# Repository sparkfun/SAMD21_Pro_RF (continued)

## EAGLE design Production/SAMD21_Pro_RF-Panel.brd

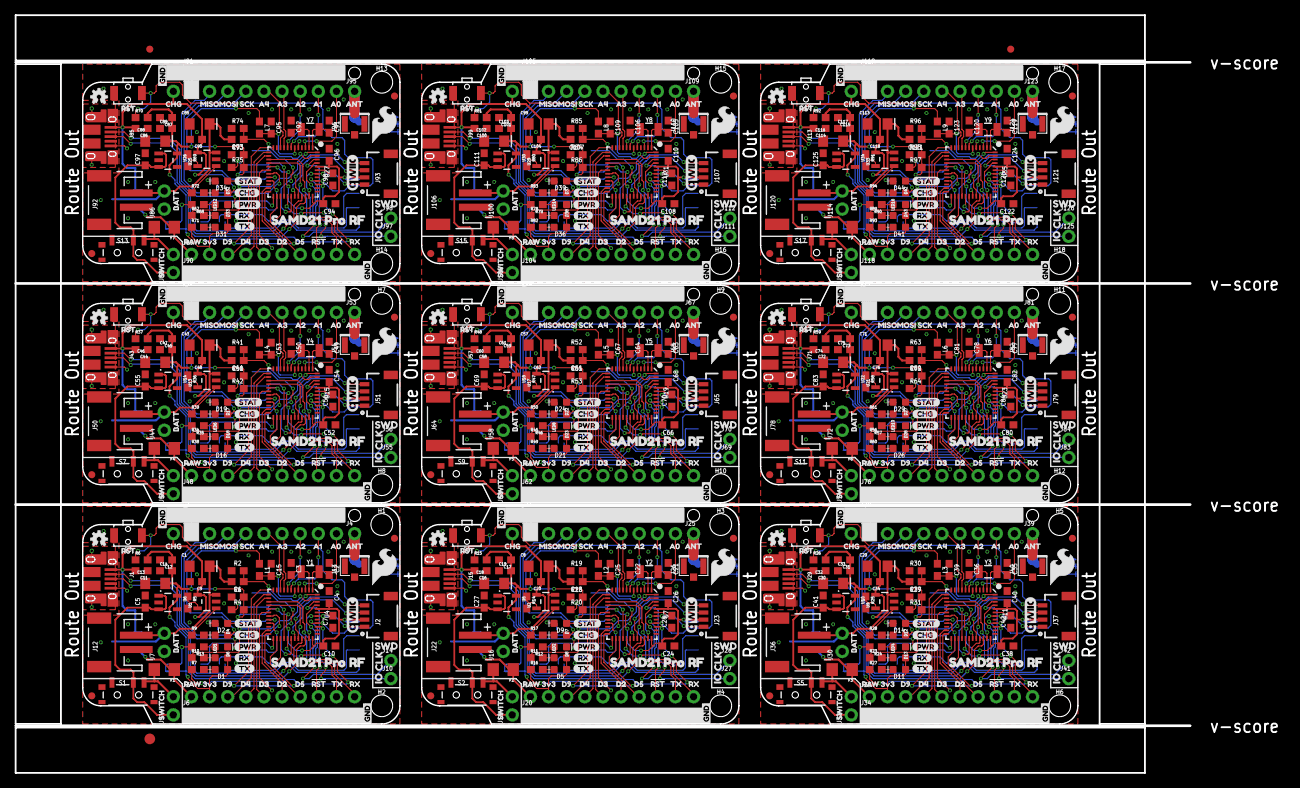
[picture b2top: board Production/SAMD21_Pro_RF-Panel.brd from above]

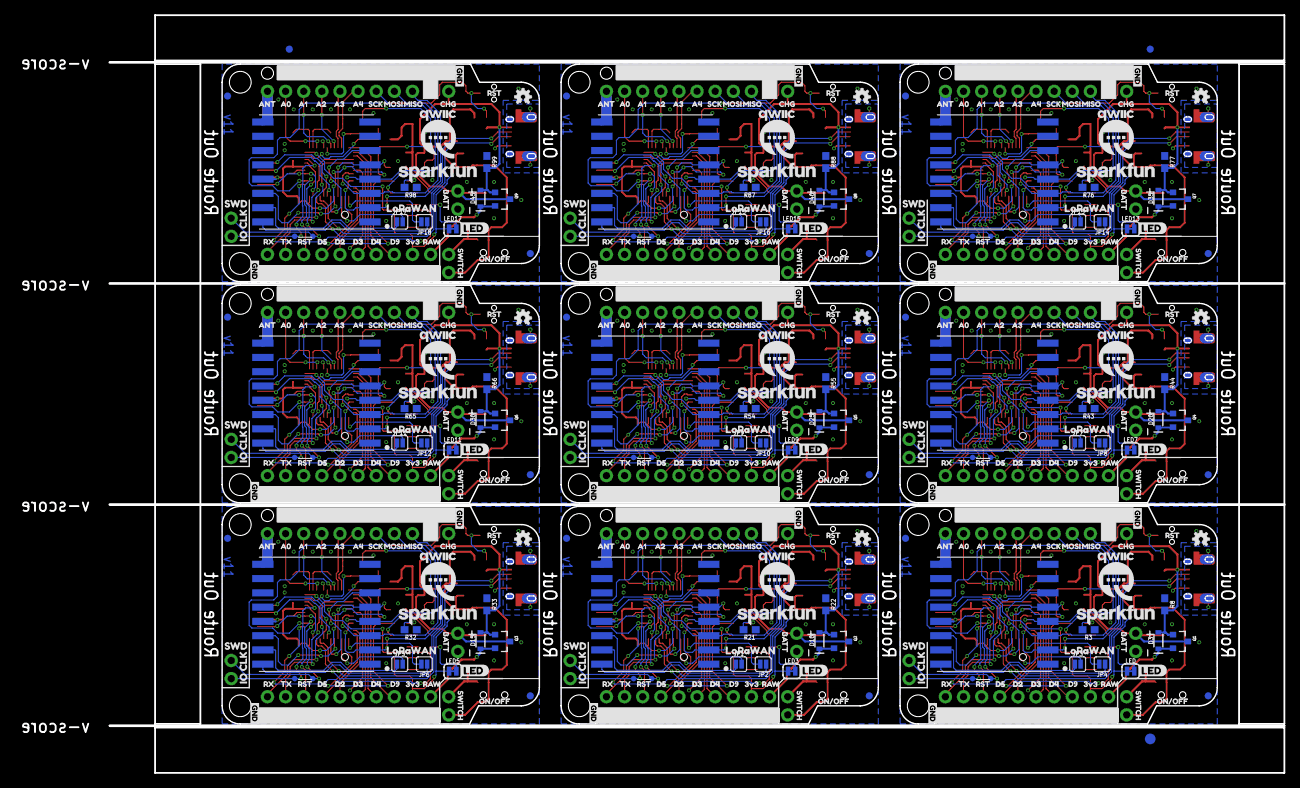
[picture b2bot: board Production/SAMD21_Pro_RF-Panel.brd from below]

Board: 2 copper layers, 164.6 x 106.2 mm, 1248 parts (426 on the bottom side), 486 nets.

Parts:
C1, C8, C13, C18, C29, C32, C43, C46, C57, C60, C71, C74, C85, C88, C99, C102, C113, C116: 10uF; EIA3216
C2, C3, C21, C22, C35, C36, C49, C50, C63, C64, C77, C78, C91, C92, C105, C106, C119, C120: 15pF; 0603
C4, C6, C10, C11, C14, C15, C16, C19, C23, C24, C25, C26, C30, C33, C37, C38, C39, C40, C44, C47, C51, C52, C53, C54, C58, C61, C65, C66, C67, C68, C72, C75, C79, C80, C81, C82, C86, C89, C93, C94, C95, C96, C100, C103, C107, C108, C109, C110, C114, C117, C121, C122, C123, C124: 0.1uF; 0603
C5, C7, C12, C17, C27, C28, C31, C41, C42, C45, C55, C56, C59, C69, C70, C73, C83, C84, C87, C97, C98, C101, C111, C112, C115, C125, C126: 1.0uF; 0603
C9, C20, C34, C48, C62, C76, C90, C104, C118: 4.7uF; 0603
D1, D5, D11, D16, D21, D26, D31, D36, D41: Green; LED-0603
D2, D4, D7, D9, D12, D14, D17, D19, D22, D24, D27, D29, D32, D34, D37, D39, D42, D44: BLUE; LED-0603
D3, D10, D15, D20, D25, D30, D35, D40, D45: 1A/23V/620mV; SOD-323
D6, D8, D13, D18, D23, D28, D33, D38, D43: Yellow; LED-0603
E$1, E$2, E$3, E$4: FIDUCIAL-1X2
E$5, E$6: FIDUCIAL-1.5X3
F1, F2, F3, F4, F5, F6, F7, F8, F9: 6V/0.5A; 1206
FD1, FD2, FD3, FD4, FD5, FD6, FD7, FD8, FD9, FD10, FD11, FD12, FD13, FD14, FD15, FD16, FD17, FD18, FD19, FD20, FD21, FD22, FD23, FD24, FD25, FD26, FD27, FD28, FD29, FD30, FD31, FD32, FD33, FD34, FD35, FD36: FIDUCIAL1X2; FIDUCIAL-1X2
H1, H2, H3, H4, H5, H6, H7, H8, H9, H10, H11, H12, H13, H14, H15, H16, H17, H18: STAND-OFFTIGHT; STAND-OFF-TIGHT
J1, J15, J29, J43, J57, J71, J85, J99, J113: USB-MICROB-PTH-MILL
J2, J23, J37, J51, J65, J79, J93, J107, J121: 1X04_1MM_RA
J3, J6, J19, J20, J33, J34, J47, J48, J61, J62, J75, J76, J89, J90, J103, J104, J117, J118: 1X10_NO_SILK
J4, J10, J14, J25, J27, J28, J39, J41, J42, J53, J55, J56, J67, J69, J70, J81, J83, J84, J95, J97, J98, J109, J111, J112, J123, J125, J126: 1X01_NO_SILK
J5, J11, J21, J24, J35, J38, J49, J52, J63, J66, J77, J80, J91, J94, J105, J108, J119, J122: 1X09_NO_SILK
J7, J16, J30, J44, J58, J72, J86, J100, J114: PTH; 1X02_NO_SILK
J8, J17, J31, J45, J59, J73, J87, J101, J115: 1X02_NO_SILK
J9, J18, J32, J46, J60, J74, J88, J102, J116: External On/Off; 1X02_NO_SILK
J12, J22, J36, J50, J64, J78, J92, J106, J120: JST; JST-2-SMD
J13, J26, J40, J54, J68, J82, J96, J110, J124: U.FL
JP1, JP2, JP3, JP4, JP5, JP6, JP7, JP8, JP9, JP10, JP11, JP12, JP13, JP14, JP15, JP16, JP17, JP18: SMT-JUMPER_2_NO_SILK
L1, L2, L3, L4, L5, L6, L7, L8, L9: 0603
LED, LED3, LED5, LED7, LED9, LED11, LED13, LED15, LED17: SMT-JUMPER_2_NC_TRACE_SILK
LED1, LED2, LED4, LED6, LED8, LED10, LED12, LED14, LED16: RED; LED-0603
LOGO1, LOGO4, LOGO7, LOGO10, LOGO13, LOGO16, LOGO19, LOGO22, LOGO25: OSHW-LOGOMINI; OSHW-LOGO-MINI
LOGO2, LOGO5, LOGO8, LOGO11, LOGO14, LOGO17, LOGO20, LOGO23, LOGO26: SFE_LOGO_NAME.1_INCH; SFE_LOGO_NAME_.1
LOGO3, LOGO6, LOGO9, LOGO12, LOGO15, LOGO18, LOGO21, LOGO24, LOGO27: QWIIC_LOGO_5MM; QWIIC_5MM
Q1, Q2, Q3, Q4, Q5, Q6, Q7, Q8, Q9: 2.5A/30V; SOT23-3@1
R1, R2, R18, R19, R29, R30, R40, R41, R51, R52, R62, R63, R73, R74, R84, R85, R95, R96: 1M; 0603
R3, R7, R9, R10, R11, R12, R13, R16, R17, R21, R23, R24, R27, R28, R32, R34, R35, R38, R39, R43, R45, R46, R49, R50, R54, R56, R57, R60, R61, R65, R67, R68, R71, R72, R76, R78, R79, R82, R83, R87, R89, R90, R93, R94, R98: 1k; 0603
R4, R6, R8, R15, R20, R22, R26, R31, R33, R37, R42, R44, R48, R53, R55, R59, R64, R66, R70, R75, R77, R81, R86, R88, R92, R97, R99: 10k; 0603
R5, R14, R25, R36, R47, R58, R69, R80, R91: 2.0k; 0603
S1, S2, S5, S7, S9, S11, S13, S15, S17: Power; SWITCH_SPST_SMD_A
S3, S4, S6, S8, S10, S12, S14, S16, S18: TACTILE_SWITCH_SMD_RIGHT_ANGLE
TP1, TP2, TP3, TP4, TP5, TP6, TP7, TP8, TP9, TP10, TP11, TP12, TP13, TP14, TP15, TP16, TP17, TP18: TEST-POINT3; PAD.03X.03
U1, U2, U9, U13, U17, U21, U25, U29, U33: MCP73831; SOT23-5
U3, U8, U12, U16, U20, U24, U28, U32, U36: RFM95W; RFM95/96/97/98W
U4, U7, U11, U15, U19, U23, U27, U31, U35: ATSAMD21G; QFN-48_NO_EXPOSED_PAD
U5, U6, U10, U14, U18, U22, U26, U30, U34: 3.3V; SOT23-5
U$1, U$120, U$189, U$258, U$327, U$396, U$465, U$534, U$603: SAMD21_PRO_RF0
U$2, U$18, U$121, U$125, U$190, U$194, U$259, U$263, U$328, U$332, U$397, U$401, U$466, U$470, U$535, U$539, U$604, U$608: D20
U$3, U$26, U$42, U$94, U$139, U$163, U$208, U$232, U$277, U$301, U$346, U$370, U$415, U$439, U$484, U$508, U$553, U$577: A43
U$4, U$43, U$67, U$95, U$140, U$164, U$209, U$233, U$278, U$302, U$347, U$371, U$416, U$440, U$485, U$509, U$554, U$578: A34
U$5, U$44, U$68, U$96, U$141, U$165, U$210, U$234, U$279, U$303, U$348, U$372, U$417, U$441, U$486, U$510, U$555, U$579: A25
U$6, U$45, U$71, U$97, U$142, U$166, U$211, U$235, U$280, U$304, U$349, U$373, U$418, U$442, U$487, U$511, U$556, U$580: A16
U$7, U$46, U$74, U$98, U$143, U$167, U$212, U$236, U$281, U$305, U$350, U$374, U$419, U$443, U$488, U$512, U$557, U$581: A07
U$8, U$47, U$75, U$99, U$144, U$168, U$213, U$237, U$282, U$306, U$351, U$375, U$420, U$444, U$489, U$513, U$558, U$582: MISO8
U$9, U$48, U$76, U$100, U$145, U$169, U$214, U$238, U$283, U$307, U$352, U$376, U$421, U$445, U$490, U$514, U$559, U$583: MOSI9
U$10, U$49, U$77, U$101, U$146, U$170, U$215, U$239, U$284, U$308, U$353, U$377, U$422, U$446, U$491, U$515, U$560, U$584: SCK10
U$11, U$50, U$78, U$102, U$147, U$171, U$216, U$240, U$285, U$309, U$354, U$378, U$423, U$447, U$492, U$516, U$561, U$585: ANT11
U$12, U$17, U$38, U$62, U$79, U$90, U$105, U$115, U$148, U$159, U$174, U$184, U$217, U$228, U$243, U$253, U$286, U$297, U$312, U$322, U$355, U$366, U$381, U$391, U$424, U$435, U$450, U$460, U$493, U$504, U$519, U$529, U$562, U$573, U$588, U$598: GND0
U$13, U$28, U$36, U$41, U$80, U$85, U$88, U$93, U$149, U$154, U$157, U$162, U$218, U$223, U$226, U$231, U$287, U$292, U$295, U$300, U$356, U$361, U$364, U$369, U$425, U$430, U$433, U$438, U$494, U$499, U$502, U$507, U$563, U$568, U$571, U$576: RST2
U$14, U$40, U$65, U$81, U$92, U$111, U$150, U$161, U$180, U$219, U$230, U$249, U$288, U$299, U$318, U$357, U$368, U$387, U$426, U$437, U$456, U$495, U$506, U$525, U$564, U$575, U$594: CHG1
U$15, U$16, U$113, U$114, U$182, U$183, U$251, U$252, U$320, U$321, U$389, U$390, U$458, U$459, U$527, U$528, U$596, U$597: D90
U$19, U$73, U$110, U$116, U$179, U$185, U$248, U$254, U$317, U$323, U$386, U$392, U$455, U$461, U$524, U$530, U$593, U$599: RX2
U$20, U$21, U$122, U$126, U$191, U$195, U$260, U$264, U$329, U$333, U$398, U$402, U$467, U$471, U$536, U$540, U$605, U$609: D30
U$22, U$31, U$123, U$127, U$192, U$196, U$261, U$265, U$330, U$334, U$399, U$403, U$468, U$472, U$537, U$541, U$606, U$610: D40
U$23, U$53, U$82, U$104, U$151, U$173, U$220, U$242, U$289, U$311, U$358, U$380, U$427, U$449, U$496, U$518, U$565, U$587: 3V320
U$24, U$52, U$83, U$103, U$152, U$172, U$221, U$241, U$290, U$310, U$359, U$379, U$428, U$448, U$497, U$517, U$566, U$586: RAW21
U$25, U$118, U$187, U$256, U$325, U$394, U$463, U$532, U$601: LORA0
U$27, U$37, U$84, U$89, U$153, U$158, U$222, U$227, U$291, U$296, U$360, U$365, U$429, U$434, U$498, U$503, U$567, U$572: SWITCH23
U$29, U$32, U$86, U$87, U$155, U$156, U$224, U$225, U$293, U$294, U$362, U$363, U$431, U$432, U$500, U$501, U$569, U$570: BATT25
U$30, U$128, U$197, U$266, U$335, U$404, U$473, U$542, U$611: QWIIC-LOGO-MEDIUM
U$33, U$124, U$193, U$262, U$331, U$400, U$469, U$538, U$607: D50
U$34, U$64, U$132, U$137, U$201, U$206, U$270, U$275, U$339, U$344, U$408, U$413, U$477, U$482, U$546, U$551, U$615, U$620: IO3
U$35, U$119, U$188, U$257, U$326, U$395, U$464, U$533, U$602: WAN1
U$39, U$91, U$160, U$229, U$298, U$367, U$436, U$505, U$574: ON#OFF0
U$51, U$131, U$200, U$269, U$338, U$407, U$476, U$545, U$614: SFE_LOGO_FLAME_.2
U$54, U$130, U$199, U$268, U$337, U$406, U$475, U$544, U$613: STAT0
U$55, U$112, U$181, U$250, U$319, U$388, U$457, U$526, U$595: D514
U$56, U$60, U$133, U$136, U$202, U$205, U$271, U$274, U$340, U$343, U$409, U$412, U$478, U$481, U$547, U$550, U$616, U$619: CLK4
U$57, U$69, U$107, U$117, U$176, U$186, U$245, U$255, U$314, U$324, U$383, U$393, U$452, U$462, U$521, U$531, U$590, U$600: TX3
U$58, U$59, U$134, U$135, U$203, U$204, U$272, U$273, U$341, U$342, U$410, U$411, U$479, U$480, U$548, U$549, U$617, U$618: SWD2
U$61, U$129, U$198, U$267, U$336, U$405, U$474, U$543, U$612: OSHW-LOGO-MINI
U$63, U$106, U$175, U$244, U$313, U$382, U$451, U$520, U$589: PWR-()-03
U$66, U$138, U$207, U$276, U$345, U$414, U$483, U$552, U$621: LED0
U$70, U$108, U$177, U$246, U$315, U$384, U$453, U$522, U$591: TX6
U$72, U$109, U$178, U$247, U$316, U$385, U$454, U$523, U$592: RX7
Y1, Y2, Y3, Y4, Y5, Y6, Y7, Y8, Y9: 32.768kHz; CRYSTAL-SMD-3.2X1.5MM

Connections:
3.3V: C4.2, C6.2, C10.2, C12.1, C13.+, C14.2, D1.A, D6.A, J2.2, J3.2, L1.1, LED.1, R4.2, R6.2, U3.3.3V, U4.17, U4.36, U4.44, U6.5
3.3V1: C17.1, C18.+, C19.2, C23.2, C24.2, C26.2, D5.A, D8.A, J19.2, J23.2, L2.1, LED3.1, R15.2, R20.2, U5.5, U7.17, U7.36, U7.44, U8.3.3V
3.3V2: C31.1, C32.+, C33.2, C37.2, C38.2, C40.2, D11.A, D13.A, J33.2, J37.2, L3.1, LED5.1, R26.2, R31.2, U10.5, U11.17, U11.36, U11.44, U12.3.3V
3.3V3: C45.1, C46.+, C47.2, C51.2, C52.2, C54.2, D16.A, D18.A, J47.2, J51.2, L4.1, LED7.1, R37.2, R42.2, U14.5, U15.17, U15.36, U15.44, U16.3.3V
3.3V4: C59.1, C60.+, C61.2, C65.2, C66.2, C68.2, D21.A, D23.A, J61.2, J65.2, L5.1, LED9.1, R48.2, R53.2, U18.5, U19.17, U19.36, U19.44, U20.3.3V
3.3V5: C73.1, C74.+, C75.2, C79.2, C80.2, C82.2, D26.A, D28.A, J75.2, J79.2, L6.1, LED11.1, R59.2, R64.2, U22.5, U23.17, U23.36, U23.44, U24.3.3V
3.3V6: C87.1, C88.+, C89.2, C93.2, C94.2, C96.2, D31.A, D33.A, J89.2, J93.2, L7.1, LED13.1, R70.2, R75.2, U26.5, U27.17, U27.36, U27.44, U28.3.3V
3.3V7: C101.1, C102.+, C103.2, C107.2, C108.2, C110.2, D36.A, D38.A, J103.2, J107.2, L8.1, LED15.1, R81.2, R86.2, U30.5, U31.17, U31.36, U31.44, U32.3.3V
3.3V8: C115.1, C116.+, C117.2, C121.2, C122.2, C124.2, D41.A, D43.A, J117.2, J121.2, L9.1, LED17.1, R92.2, R97.2, U34.5, U35.17, U35.36, U35.44, U36.3.3V
!RFM_CS: R4.1, U3.NSS, U4.28
!RFM_CS1: R20.1, U7.28, U8.NSS
!RFM_CS2: R31.1, U11.28, U12.NSS
!RFM_CS3: R42.1, U15.28, U16.NSS
!RFM_CS4: R53.1, U19.28, U20.NSS
!RFM_CS5: R64.1, U23.28, U24.NSS
!RFM_CS6: R75.1, U27.28, U28.NSS
!RFM_CS7: R86.1, U31.28, U32.NSS
!RFM_CS8: R97.1, U35.28, U36.NSS
!RFM_RST: U3.!RESET, U4.30
!RFM_RST1: U7.30, U8.!RESET
!RFM_RST2: U11.30, U12.!RESET
!RFM_RST3: U15.30, U16.!RESET
!RFM_RST4: U19.30, U20.!RESET
!RFM_RST5: U23.30, U24.!RESET
!RFM_RST6: U27.30, U28.!RESET
!RFM_RST7: U31.30, U32.!RESET
!RFM_RST8: U35.30, U36.!RESET
!RST: J3.8, R6.1, S3.1, U4.40
!RST1: J19.8, R15.1, S4.1, U7.40
!RST2: J33.8, R26.1, S6.1, U11.40
!RST3: J47.8, R37.1, S8.1, U15.40
!RST4: J61.8, R48.1, S10.1, U19.40
!RST5: J75.8, R59.1, S12.1, U23.40
!RST6: J89.8, R70.1, S14.1, U27.40
!RST7: J103.8, R81.1, S16.1, U31.40
!RST8: J117.8, R92.1, S18.1, U35.40
A0: J11.9, U4.3
A1: J11.8, U4.7
A2: J11.7, U4.8
A3: J11.6, U4.9
A4: J11.5, U4.10
A5: J24.9, U7.3
A6: J24.8, U7.7
A7: J24.7, U7.8
A8: J24.6, U7.9
A9: J24.5, U7.10
A10: J38.9, U11.3
A11: J38.8, U11.7
A12: J38.7, U11.8
A13: J38.6, U11.9
A14: J38.5, U11.10
A15: J52.9, U15.3
A16: J52.8, U15.7
A17: J52.7, U15.8
A18: J52.6, U15.9
A19: J52.5, U15.10
A20: J66.9, U19.3
A21: J66.8, U19.7
A22: J66.7, U19.8
A23: J66.6, U19.9
A24: J66.5, U19.10
A25: J80.9, U23.3
A26: J80.8, U23.7
A27: J80.7, U23.8
A28: J80.6, U23.9
A29: J80.5, U23.10
A30: J94.9, U27.3
A31: J94.8, U27.7
A32: J94.7, U27.8
A33: J94.6, U27.9
A34: J94.5, U27.10
A35: J108.9, U31.3
A36: J108.8, U31.7
A37: J108.7, U31.8
A38: J108.6, U31.9
A39: J108.5, U31.10
A40: J122.9, U35.3
A41: J122.8, U35.7
A42: J122.7, U35.8
A43: J122.6, U35.9
A44: J122.5, U35.10
ANT: J4.1, J13.FEED, U3.ANT
ANT1: J25.1, J26.FEED, U8.ANT
ANT2: J39.1, J40.FEED, U12.ANT
ANT3: J53.1, J54.FEED, U16.ANT
ANT4: J67.1, J68.FEED, U20.ANT
ANT5: J81.1, J82.FEED, U24.ANT
ANT6: J95.1, J96.FEED, U28.ANT
ANT7: J109.1, J110.FEED, U32.ANT
ANT8: J123.1, J124.FEED, U36.ANT
CHARGE_STAT: R9.1, U1.1
CHARGE_STAT1: R17.1, U2.1
CHARGE_STAT2: R28.1, U9.1
CHARGE_STAT3: R39.1, U13.1
CHARGE_STAT4: R50.1, U17.1
CHARGE_STAT5: R61.1, U21.1
CHARGE_STAT6: R72.1, U25.1
CHARGE_STAT7: R83.1, U29.1
CHARGE_STAT8: R94.1, U33.1
D1: J19.4, U7.13
D2: J3.6, U4.23
D3: J3.5, U4.14
D4: J3.4, U4.13
D5: J3.7, U4.24
D6: J19.6, U7.23
D7: J19.5, U7.14
D8: J19.7, U7.24
D9: J3.3, U4.12
D10: J19.3, U7.12
D10_LORA-WAN: JP3.2, U4.27
D10_LORA-WAN1: JP1.2, U7.27
D10_LORA-WAN2: JP5.2, U11.27
D10_LORA-WAN3: JP7.2, U15.27
D10_LORA-WAN4: JP9.2, U19.27
D10_LORA-WAN5: JP11.2, U23.27
D10_LORA-WAN6: JP13.2, U27.27
D10_LORA-WAN7: JP15.2, U31.27
D10_LORA-WAN8: JP17.2, U35.27
D11: J33.4, U11.13
D11_LORA-WAN: JP4.2, U4.25
D11_LORA-WAN1: JP2.2, U7.25
D11_LORA-WAN2: JP6.2, U11.25
D11_LORA-WAN3: JP8.2, U15.25
D11_LORA-WAN4: JP10.2, U19.25
D11_LORA-WAN5: JP12.2, U23.25
D11_LORA-WAN6: JP14.2, U27.25
D11_LORA-WAN7: JP16.2, U31.25
D11_LORA-WAN8: JP18.2, U35.25
D12: J33.6, U11.23
D13: J33.5, U11.14
D14: J33.7, U11.24
D15: J33.3, U11.12
D16: J47.4, U15.13
D17: J47.6, U15.23
D18: J47.5, U15.14
D19: J47.7, U15.24
D20: J47.3, U15.12
D21: J61.4, U19.13
D22: J61.6, U19.23
D23: J61.5, U19.14
D24: J61.7, U19.24
D25: J61.3, U19.12
D26: J75.4, U23.13
D27: J75.6, U23.23
D28: J75.5, U23.14
D29: J75.7, U23.24
D30: J75.3, U23.12
D31: J89.4, U27.13
D32: J89.6, U27.23
D33: J89.5, U27.14
D34: J89.7, U27.24
D35: J89.3, U27.12
D36: J103.4, U31.13
D37: J103.6, U31.23
D38: J103.5, U31.14
D39: J103.7, U31.24
D40: J103.3, U31.12
D41: J117.4, U35.13
D42: J117.6, U35.23
D43: J117.5, U35.14
D44: J117.7, U35.24
D45: J117.3, U35.12
D+: J1.D+, U4.34
D+1: J15.D+, U7.34
D+2: J29.D+, U11.34
D+3: J43.D+, U15.34
D+4: J57.D+, U19.34
D+5: J71.D+, U23.34
D+6: J85.D+, U27.34
D+7: J99.D+, U31.34
D+8: J113.D+, U35.34
D-: J1.D-, U4.33
D-1: J15.D-, U7.33
D-2: J29.D-, U11.33
D-3: J43.D-, U15.33
D-4: J57.D-, U19.33
D-5: J71.D-, U23.33
D-6: J85.D-, U27.33
D-7: J99.D-, U31.33
D-8: J113.D-, U35.33
GND: C1.-, C2.1, C3.1, C4.1, C5.2, C6.1, C7.1, C9.2, C10.1, C11.1, C12.2, C13.-, C14.1, C15.1, J1.GND, J2.1, J5.1, J5.2, J5.3, J5.4, J5.5, J5.6, J5.7, J5.8, J5.9, J6.1, J6.2, J6.3, J6.4, J6.5, J6.6, J6.7, J6.8, J6.9, J6.10, J7.1, J8.1, J11.1, J12.1, J13.1, J13.2, LED1.C, R2.1, R3.1, R5.2, R8.1, S3.2, U1.2, U3.GND@1, U3.GND@2, U3.GND@3, U4.5, U4.18, U4.35, U4.42, U6.2
GND1: C8.-, C16.1, C17.2, C18.-, C19.1, C20.2, C21.1, C22.1, C23.1, C24.1, C25.1, C26.1, C27.2, C28.1, J15.GND, J16.1, J17.1, J20.1, J20.2, J20.3, J20.4, J20.5, J20.6, J20.7, J20.8, J20.9, J20.10, J21.1, J21.2, J21.3, J21.4, J21.5, J21.6, J21.7, J21.8, J21.9, J22.1, J23.1, J24.1, J26.1, J26.2, LED2.C, R14.2, R19.1, R21.1, R22.1, S4.2, U2.2, U5.2, U7.5, U7.18, U7.35, U7.42, U8.GND@1, U8.GND@2, U8.GND@3
GND2: C29.-, C30.1, C31.2, C32.-, C33.1, C34.2, C35.1, C36.1, C37.1, C38.1, C39.1, C40.1, C41.2, C42.1, J29.GND, J30.1, J31.1, J34.1, J34.2, J34.3, J34.4, J34.5, J34.6, J34.7, J34.8, J34.9, J34.10, J35.1, J35.2, J35.3, J35.4, J35.5, J35.6, J35.7, J35.8, J35.9, J36.1, J37.1, J38.1, J40.1, J40.2, LED4.C, R25.2, R30.1, R32.1, R33.1, S6.2, U9.2, U10.2, U11.5, U11.18, U11.35, U11.42, U12.GND@1, U12.GND@2, U12.GND@3
GND3: C43.-, C44.1, C45.2, C46.-, C47.1, C48.2, C49.1, C50.1, C51.1, C52.1, C53.1, C54.1, C55.2, C56.1, J43.GND, J44.1, J45.1, J48.1, J48.2, J48.3, J48.4, J48.5, J48.6, J48.7, J48.8, J48.9, J48.10, J49.1, J49.2, J49.3, J49.4, J49.5, J49.6, J49.7, J49.8, J49.9, J50.1, J51.1, J52.1, J54.1, J54.2, LED6.C, R36.2, R41.1, R43.1, R44.1, S8.2, U13.2, U14.2, U15.5, U15.18, U15.35, U15.42, U16.GND@1, U16.GND@2, U16.GND@3
GND4: C57.-, C58.1, C59.2, C60.-, C61.1, C62.2, C63.1, C64.1, C65.1, C66.1, C67.1, C68.1, C69.2, C70.1, J57.GND, J58.1, J59.1, J62.1, J62.2, J62.3, J62.4, J62.5, J62.6, J62.7, J62.8, J62.9, J62.10, J63.1, J63.2, J63.3, J63.4, J63.5, J63.6, J63.7, J63.8, J63.9, J64.1, J65.1, J66.1, J68.1, J68.2, LED8.C, R47.2, R52.1, R54.1, R55.1, S10.2, U17.2, U18.2, U19.5, U19.18, U19.35, U19.42, U20.GND@1, U20.GND@2, U20.GND@3
GND5: C71.-, C72.1, C73.2, C74.-, C75.1, C76.2, C77.1, C78.1, C79.1, C80.1, C81.1, C82.1, C83.2, C84.1, J71.GND, J72.1, J73.1, J76.1, J76.2, J76.3, J76.4, J76.5, J76.6, J76.7, J76.8, J76.9, J76.10, J77.1, J77.2, J77.3, J77.4, J77.5, J77.6, J77.7, J77.8, J77.9, J78.1, J79.1, J80.1, J82.1, J82.2, LED10.C, R58.2, R63.1, R65.1, R66.1, S12.2, U21.2, U22.2, U23.5, U23.18, U23.35, U23.42, U24.GND@1, U24.GND@2, U24.GND@3
GND6: C85.-, C86.1, C87.2, C88.-, C89.1, C90.2, C91.1, C92.1, C93.1, C94.1, C95.1, C96.1, C97.2, C98.1, J85.GND, J86.1, J87.1, J90.1, J90.2, J90.3, J90.4, J90.5, J90.6, J90.7, J90.8, J90.9, J90.10, J91.1, J91.2, J91.3, J91.4, J91.5, J91.6, J91.7, J91.8, J91.9, J92.1, J93.1, J94.1, J96.1, J96.2, LED12.C, R69.2, R74.1, R76.1, R77.1, S14.2, U25.2, U26.2, U27.5, U27.18, U27.35, U27.42, U28.GND@1, U28.GND@2, U28.GND@3
GND7: C99.-, C100.1, C101.2, C102.-, C103.1, C104.2, C105.1, C106.1, C107.1, C108.1, C109.1, C110.1, C111.2, C112.1, J99.GND, J100.1, J101.1, J104.1, J104.2, J104.3, J104.4, J104.5, J104.6, J104.7, J104.8, J104.9, J104.10, J105.1, J105.2, J105.3, J105.4, J105.5, J105.6, J105.7, J105.8, J105.9, J106.1, J107.1, J108.1, J110.1, J110.2, LED14.C, R80.2, R85.1, R87.1, R88.1, S16.2, U29.2, U30.2, U31.5, U31.18, U31.35, U31.42, U32.GND@1, U32.GND@2, U32.GND@3
GND8: C113.-, C114.1, C115.2, C116.-, C117.1, C118.2, C119.1, C120.1, C121.1, C122.1, C123.1, C124.1, C125.2, C126.1, J113.GND, J114.1, J115.1, J118.1, J118.2, J118.3, J118.4, J118.5, J118.6, J118.7, J118.8, J118.9, J118.10, J119.1, J119.2, J119.3, J119.4, J119.5, J119.6, J119.7, J119.8, J119.9, J120.1, J121.1, J122.1, J124.1, J124.2, LED16.C, R91.2, R96.1, R98.1, R99.1, S18.2, U33.2, U34.2, U35.5, U35.18, U35.35, U35.42, U36.GND@1, U36.GND@2, U36.GND@3
MISO: J11.2, U3.MISO, U4.21
MISO1: J24.2, U7.21, U8.MISO
MISO2: J38.2, U11.21, U12.MISO
MISO3: J52.2, U15.21, U16.MISO
MISO4: J66.2, U19.21, U20.MISO
MISO5: J80.2, U23.21, U24.MISO
MISO6: J94.2, U27.21, U28.MISO
MISO7: J108.2, U31.21, U32.MISO
MISO8: J122.2, U35.21, U36.MISO
MOSI: J11.3, U3.MOSI, U4.19
MOSI1: J24.3, U7.19, U8.MOSI
MOSI2: J38.3, U11.19, U12.MOSI
MOSI3: J52.3, U15.19, U16.MOSI
MOSI4: J66.3, U19.19, U20.MOSI
MOSI5: J80.3, U23.19, U24.MOSI
MOSI6: J94.3, U27.19, U28.MOSI
MOSI7: J108.3, U31.19, U32.MOSI
MOSI8: J122.3, U35.19, U36.MOSI
unnamed: D6.C, R10.2
unnamed: D1.C, R7.2
unnamed: D2.C, R3.2
unnamed: C7.2, U4.43
unnamed: LED.2, R13.2
unnamed: C2.2, U4.1, Y1.P$2
unnamed: C3.2, U4.2, Y1.P$1
unnamed: D4.C, R9.2
unnamed: F1.2, J9.2, S1.1
unnamed: F2.2, J18.2, S2.1
unnamed: R5.1, U1.5
unnamed: R14.1, U2.5
unnamed: D7.C, R17.2
unnamed: LED2.A, R12.1
unnamed: D8.C, R11.2
unnamed: D5.C, R16.2
unnamed: JP3.1, U3.DIO1
unnamed: JP4.1, U3.DIO2
unnamed: C21.2, U7.1, Y2.P$2
unnamed: C22.2, U7.2, Y2.P$1
unnamed: D9.C, R21.2
unnamed: JP1.1, U8.DIO1
unnamed: JP2.1, U8.DIO2
unnamed: C28.2, U7.43
unnamed: LED3.2, R12.2
unnamed: F3.2, J32.2, S5.1
unnamed: R25.1, U9.5
unnamed: D12.C, R28.2
unnamed: LED4.A, R24.1
unnamed: D13.C, R23.2
unnamed: D11.C, R27.2
unnamed: C35.2, U11.1, Y3.P$2
unnamed: C36.2, U11.2, Y3.P$1
unnamed: D14.C, R32.2
unnamed: JP5.1, U12.DIO1
unnamed: JP6.1, U12.DIO2
unnamed: C42.2, U11.43
unnamed: LED1.A, R13.1
unnamed: LED5.2, R24.2
unnamed: F4.2, J46.2, S7.1
unnamed: R36.1, U13.5
unnamed: D17.C, R39.2
unnamed: LED6.A, R35.1
unnamed: D18.C, R34.2
unnamed: D16.C, R38.2
unnamed: C49.2, U15.1, Y4.P$2
unnamed: C50.2, U15.2, Y4.P$1
unnamed: D19.C, R43.2
unnamed: JP7.1, U16.DIO1
unnamed: JP8.1, U16.DIO2
unnamed: C56.2, U15.43
unnamed: LED7.2, R35.2
unnamed: F5.2, J60.2, S9.1
unnamed: R47.1, U17.5
unnamed: D22.C, R50.2
unnamed: LED8.A, R46.1
unnamed: D23.C, R45.2
unnamed: D21.C, R49.2
unnamed: C63.2, U19.1, Y5.P$2
unnamed: C64.2, U19.2, Y5.P$1
unnamed: D24.C, R54.2
unnamed: JP9.1, U20.DIO1
unnamed: JP10.1, U20.DIO2
unnamed: C70.2, U19.43
unnamed: LED9.2, R46.2
unnamed: F6.2, J74.2, S11.1
unnamed: R58.1, U21.5
unnamed: D27.C, R61.2
unnamed: LED10.A, R57.1
unnamed: D28.C, R56.2
unnamed: D26.C, R60.2
unnamed: C77.2, U23.1, Y6.P$2
unnamed: C78.2, U23.2, Y6.P$1
unnamed: D29.C, R65.2
unnamed: JP11.1, U24.DIO1
unnamed: JP12.1, U24.DIO2
unnamed: C84.2, U23.43
unnamed: LED11.2, R57.2
unnamed: F7.2, J88.2, S13.1
unnamed: R69.1, U25.5
unnamed: D32.C, R72.2
unnamed: LED12.A, R68.1
unnamed: D33.C, R67.2
unnamed: D31.C, R71.2
unnamed: C91.2, U27.1, Y7.P$2
unnamed: C92.2, U27.2, Y7.P$1
unnamed: D34.C, R76.2
unnamed: JP13.1, U28.DIO1
unnamed: JP14.1, U28.DIO2
unnamed: C98.2, U27.43
unnamed: LED13.2, R68.2
unnamed: F8.2, J102.2, S15.1
unnamed: R80.1, U29.5
unnamed: D37.C, R83.2
unnamed: LED14.A, R79.1
unnamed: D38.C, R78.2
unnamed: D36.C, R82.2
unnamed: C105.2, U31.1, Y8.P$2
unnamed: C106.2, U31.2, Y8.P$1
unnamed: D39.C, R87.2
unnamed: JP15.1, U32.DIO1
unnamed: JP16.1, U32.DIO2
unnamed: C112.2, U31.43
unnamed: LED15.2, R79.2
unnamed: F9.2, J116.2, S17.1
unnamed: R91.1, U33.5
unnamed: D42.C, R94.2
unnamed: LED16.A, R90.1
unnamed: D43.C, R89.2
unnamed: D41.C, R93.2
unnamed: C119.2, U35.1, Y9.P$2
unnamed: C120.2, U35.2, Y9.P$1
unnamed: D44.C, R98.2
unnamed: JP17.1, U36.DIO1
unnamed: JP18.1, U36.DIO2
unnamed: C126.2, U35.43
unnamed: LED17.2, R90.2
RAW: D3.C, F1.1, J3.1, Q1.2
RAW1: D10.C, F2.1, J19.1, Q2.2
RAW2: D15.C, F3.1, J33.1, Q3.2
RAW3: D20.C, F4.1, J47.1, Q4.2
RAW4: D25.C, F5.1, J61.1, Q5.2
RAW5: D30.C, F6.1, J75.1, Q6.2
RAW6: D35.C, F7.1, J89.1, Q7.2
RAW7: D40.C, F8.1, J103.1, Q8.2
RAW8: D45.C, F9.1, J117.1, Q9.2
RFM_INT: U3.DIO0, U4.29
RFM_INT1: U7.29, U8.DIO0
RFM_INT2: U11.29, U12.DIO0
RFM_INT3: U15.29, U16.DIO0
RFM_INT4: U19.29, U20.DIO0
RFM_INT5: U23.29, U24.DIO0
RFM_INT6: U27.29, U28.DIO0
RFM_INT7: U31.29, U32.DIO0
RFM_INT8: U35.29, U36.DIO0
RXI: J3.10, U4.16
RXI1: J19.10, U7.16
RXI2: J33.10, U11.16
RXI3: J47.10, U15.16
RXI4: J61.10, U19.16
RXI5: J75.10, U23.16
RXI6: J89.10, U27.16
RXI7: J103.10, U31.16
RXI8: J117.10, U35.16
RX_LED: R10.1, U4.48
RX_LED1: R11.1, U7.48
RX_LED2: R23.1, U11.48
RX_LED3: R34.1, U15.48
RX_LED4: R45.1, U19.48
RX_LED5: R56.1, U23.48
RX_LED6: R67.1, U27.48
RX_LED7: R78.1, U31.48
RX_LED8: R89.1, U35.48
SCK: J11.4, U3.SCK, U4.20
SCK1: J24.4, U7.20, U8.SCK
SCK2: J38.4, U11.20, U12.SCK
SCK3: J52.4, U15.20, U16.SCK
SCK4: J66.4, U19.20, U20.SCK
SCK5: J80.4, U23.20, U24.SCK
SCK6: J94.4, U27.20, U28.SCK
SCK7: J108.4, U31.20, U32.SCK
SCK8: J122.4, U35.20, U36.SCK
SCL: J2.4, U4.32
SCL1: J23.4, U7.32
SCL2: J37.4, U11.32
SCL3: J51.4, U15.32
SCL4: J65.4, U19.32
SCL5: J79.4, U23.32
SCL6: J93.4, U27.32
SCL7: J107.4, U31.32
SCL8: J121.4, U35.32
SDA: J2.3, U4.31
SDA1: J23.3, U7.31
SDA2: J37.3, U11.31
SDA3: J51.3, U15.31
SDA4: J65.3, U19.31
SDA5: J79.3, U23.31
SDA6: J93.3, U27.31
SDA7: J107.3, U31.31
SDA8: J121.3, U35.31
SHLD: J1.SHIELD, J1.SHIELD2, J1.SHIELD3, J1.SHIELD4, J1.SHIELD5, J1.SHIELD6, J1.SHIELD7, J1.SHIELD8, J1.SHIELD9, J1.SHIELD10
SHLD1: J15.SHIELD, J15.SHIELD2, J15.SHIELD3, J15.SHIELD4, J15.SHIELD5, J15.SHIELD6, J15.SHIELD7, J15.SHIELD8, J15.SHIELD9, J15.SHIELD10
SHLD2: J29.SHIELD, J29.SHIELD2, J29.SHIELD3, J29.SHIELD4, J29.SHIELD5, J29.SHIELD6, J29.SHIELD7, J29.SHIELD8, J29.SHIELD9, J29.SHIELD10
SHLD3: J43.SHIELD, J43.SHIELD2, J43.SHIELD3, J43.SHIELD4, J43.SHIELD5, J43.SHIELD6, J43.SHIELD7, J43.SHIELD8, J43.SHIELD9, J43.SHIELD10
SHLD4: J57.SHIELD, J57.SHIELD2, J57.SHIELD3, J57.SHIELD4, J57.SHIELD5, J57.SHIELD6, J57.SHIELD7, J57.SHIELD8, J57.SHIELD9, J57.SHIELD10
SHLD5: J71.SHIELD, J71.SHIELD2, J71.SHIELD3, J71.SHIELD4, J71.SHIELD5, J71.SHIELD6, J71.SHIELD7, J71.SHIELD8, J71.SHIELD9, J71.SHIELD10
SHLD6: J85.SHIELD, J85.SHIELD2, J85.SHIELD3, J85.SHIELD4, J85.SHIELD5, J85.SHIELD6, J85.SHIELD7, J85.SHIELD8, J85.SHIELD9, J85.SHIELD10
SHLD7: J99.SHIELD, J99.SHIELD2, J99.SHIELD3, J99.SHIELD4, J99.SHIELD5, J99.SHIELD6, J99.SHIELD7, J99.SHIELD8, J99.SHIELD9, J99.SHIELD10
SHLD8: J113.SHIELD, J113.SHIELD2, J113.SHIELD3, J113.SHIELD4, J113.SHIELD5, J113.SHIELD6, J113.SHIELD7, J113.SHIELD8, J113.SHIELD9, J113.SHIELD10
STAT_LED: D2.A, U4.26
STAT_LED1: D9.A, U7.26
STAT_LED2: D14.A, U11.26
STAT_LED3: D19.A, U15.26
STAT_LED4: D24.A, U19.26
STAT_LED5: D29.A, U23.26
STAT_LED6: D34.A, U27.26
STAT_LED7: D39.A, U31.26
STAT_LED8: D44.A, U35.26
SWDCLK: J14.1, TP2.P$1, U4.45
SWDCLK1: J28.1, TP4.P$1, U7.45
SWDCLK2: J42.1, TP6.P$1, U11.45
SWDCLK3: J56.1, TP8.P$1, U15.45
SWDCLK4: J70.1, TP10.P$1, U19.45
SWDCLK5: J84.1, TP12.P$1, U23.45
SWDCLK6: J98.1, TP14.P$1, U27.45
SWDCLK7: J112.1, TP16.P$1, U31.45
SWDCLK8: J126.1, TP18.P$1, U35.45
SWDIO: J10.1, TP1.P$1, U4.46
SWDIO1: J27.1, TP3.P$1, U7.46
SWDIO2: J41.1, TP5.P$1, U11.46
SWDIO3: J55.1, TP7.P$1, U15.46
SWDIO4: J69.1, TP9.P$1, U19.46
SWDIO5: J83.1, TP11.P$1, U23.46
SWDIO6: J97.1, TP13.P$1, U27.46
SWDIO7: J111.1, TP15.P$1, U31.46
SWDIO8: J125.1, TP17.P$1, U35.46
TXO: J3.9, U4.15
TXO1: J19.9, U7.15
TXO2: J33.9, U11.15
TXO3: J47.9, U15.15
TXO4: J61.9, U19.15
TXO5: J75.9, U23.15
TXO6: J89.9, U27.15
TXO7: J103.9, U31.15
TXO8: J117.9, U35.15
TX_LED: R7.1, U4.39
TX_LED1: R16.1, U7.39
TX_LED2: R27.1, U11.39
TX_LED3: R38.1, U15.39
TX_LED4: R49.1, U19.39
TX_LED5: R60.1, U23.39
TX_LED6: R71.1, U27.39
TX_LED7: R82.1, U31.39
TX_LED8: R93.1, U35.39
VBATT_LVL: R1.1, R2.2, U4.47
VBATT_LVL1: R18.1, R19.2, U7.47
VBATT_LVL2: R29.1, R30.2, U11.47
VBATT_LVL3: R40.1, R41.2, U15.47
VBATT_LVL4: R51.1, R52.2, U19.47
VBATT_LVL5: R62.1, R63.2, U23.47
VBATT_LVL6: R73.1, R74.2, U27.47
VBATT_LVL7: R84.1, R85.2, U31.47
VBATT_LVL8: R95.1, R96.2, U35.47
VDDANA: C15.2, L1.2, U4.6
VDDANA1: C25.2, L2.2, U7.6
VDDANA2: C39.2, L3.2, U11.6
VDDANA3: C53.2, L4.2, U15.6
VDDANA4: C67.2, L5.2, U19.6
VDDANA5: C81.2, L6.2, U23.6
VDDANA6: C95.2, L7.2, U27.6
VDDANA7: C109.2, L8.2, U31.6
VDDANA8: C123.2, L9.2, U35.6
VIN: C5.1, J9.1, S1.2, U6.1, U6.3
VIN1: C27.1, J18.1, S2.2, U5.1, U5.3
VIN2: C41.1, J32.1, S5.2, U10.1, U10.3
VIN3: C55.1, J46.1, S7.2, U14.1, U14.3
VIN4: C69.1, J60.1, S9.2, U18.1, U18.3
VIN5: C83.1, J74.1, S11.2, U22.1, U22.3
VIN6: C97.1, J88.1, S13.2, U26.1, U26.3
VIN7: C111.1, J102.1, S15.2, U30.1, U30.3
VIN8: C125.1, J116.1, S17.2, U34.1, U34.3
V_BATT: C1.+, J7.2, J12.2, Q1.3, R1.2, U1.3
V_BATT1: C8.+, J16.2, J22.2, Q2.3, R18.2, U2.3
V_BATT2: C29.+, J30.2, J36.2, Q3.3, R29.2, U9.3
V_BATT3: C43.+, J44.2, J50.2, Q4.3, R40.2, U13.3
V_BATT4: C57.+, J58.2, J64.2, Q5.3, R51.2, U17.3
V_BATT5: C71.+, J72.2, J78.2, Q6.3, R62.2, U21.3
V_BATT6: C85.+, J86.2, J92.2, Q7.3, R73.2, U25.3
V_BATT7: C99.+, J100.2, J106.2, Q8.3, R84.2, U29.3
V_BATT8: C113.+, J114.2, J120.2, Q9.3, R95.2, U33.3
V_USB: C9.1, C11.2, D3.A, D4.A, J1.VBUS, J8.2, Q1.1, R8.2, U1.4
V_USB1: C16.2, C20.1, D7.A, D10.A, J15.VBUS, J17.2, Q2.1, R22.2, U2.4
V_USB2: C30.2, C34.1, D12.A, D15.A, J29.VBUS, J31.2, Q3.1, R33.2, U9.4
V_USB3: C44.2, C48.1, D17.A, D20.A, J43.VBUS, J45.2, Q4.1, R44.2, U13.4
V_USB4: C58.2, C62.1, D22.A, D25.A, J57.VBUS, J59.2, Q5.1, R55.2, U17.4
V_USB5: C72.2, C76.1, D27.A, D30.A, J71.VBUS, J73.2, Q6.1, R66.2, U21.4
V_USB6: C86.2, C90.1, D32.A, D35.A, J85.VBUS, J87.2, Q7.1, R77.2, U25.4
V_USB7: C100.2, C104.1, D37.A, D40.A, J99.VBUS, J101.2, Q8.1, R88.2, U29.4
V_USB8: C114.2, C118.1, D42.A, D45.A, J113.VBUS, J115.2, Q9.1, R99.2, U33.4
